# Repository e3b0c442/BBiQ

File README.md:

# BBiQ
Bespoke internet-connected barbecue thermometer

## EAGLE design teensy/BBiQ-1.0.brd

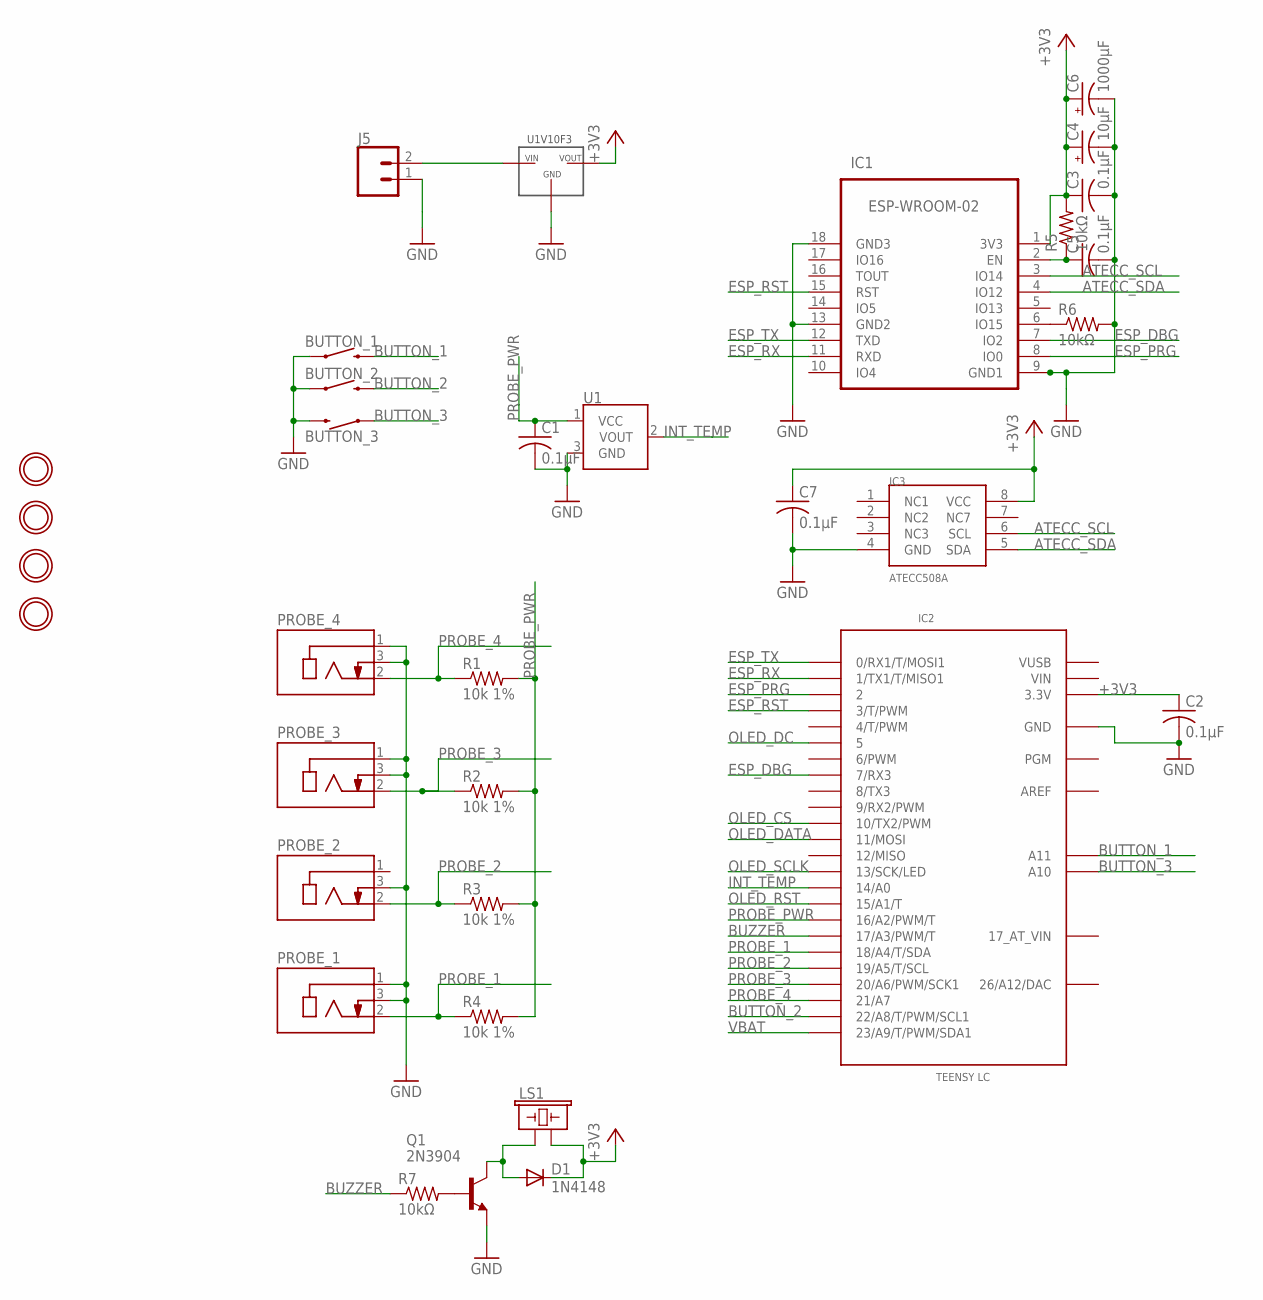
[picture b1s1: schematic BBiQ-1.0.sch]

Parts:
BUTTON_1, BUTTON_2, BUTTON_3: MOMENTARY-SWITCH-SPST-PTH-6.0MM; TACTILE_SWITCH_PTH_6.0MM
C1, C2, C3, C5, C7: 0.1µF; C025-025X050
C4: 10µF; E2-5
C6: 1000µF; E3,5-8
D1: 1N4148; DO35-7
IC1: ESP-WROOM-02
IC2: TEENSY LC; TEENSY_3.0-3.2&LC_ALL_PINS
IC3: ATECC508A; SOIC8
J5: CONN_02JST-PTH-2; JST-2-PTH
LS1: BUZZER-PTH; BUZZER-12MM
PROBE_1, PROBE_2, PROBE_3, PROBE_4: MJ-2506N; CUI_MJ-2506N
Q1: 2N3904; TO92
R1, R2, R3, R4: 10k 1%; 0207/7
R5, R6, R7: 10kΩ; 0207/7
U1: TMP36GT9; TO-92
U$2: U1V10F3
U$3, U$4, U$5, U$6: MOUNTINGHOLE2.5; MOUNTINGHOLE_2.5_PLATED

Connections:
26/A12/DAC: IC2.RESET/DAC (26/A12/DAC)
+3V3: C2.1, C3.1, C4.+, C6.+, C7.1, D1.C, IC1.1 (3V3), IC2.3.3V, IC2.3.3V1 (3.3V), IC3.8 (VCC), LS1.- (2), R5.2, U$2.VOUT
AREF: IC2.AREF
ATECC_SCL: IC1.3 (IO14), IC3.6 (SCL)
ATECC_SDA: IC1.4 (IO12), IC3.5 (SDA)
BUTTON_1: BUTTON_1.3 (2), IC2.A11
BUTTON_2: BUTTON_2.3 (2), IC2.22/A8 (22/A8/T/PWM/SCL1)
BUTTON_3: BUTTON_3.1, IC2.A10
BUZZER: IC2.17/A3 (17/A3/PWM/T), R7.1
ESP_DBG: IC1.7 (IO2), IC2.7 (7/RX3)
ESP_EN: C5.1, IC1.2 (EN), R5.1
ESP_PRG: IC1.8 (IO0), IC2.2
ESP_RST: IC1.15 (RST), IC2.3 (3/T/PWM)
ESP_RX: IC1.11 (RXD), IC2.1 (1/TX1/T/MISO1)
ESP_TX: IC1.12 (TXD), IC2.0 (0/RX1/T/MOSI1)
GND: BUTTON_1.1, BUTTON_2.1, BUTTON_3.3 (2), C1.2, C2.2, C3.2, C4.-, C5.2, C6.-, C7.2, IC1.9 (GND1), IC1.13 (GND2), IC1.18 (GND3), IC1.19 (GND0), IC2.AGND (GND), IC2.GND, IC2.GND1 (GND), IC3.4 (GND), J5.1, PROBE_1.1, PROBE_1.3, PROBE_2.3, PROBE_3.1, PROBE_3.3, PROBE_4.1, PROBE_4.3, Q1.3 (E), R6.2, U1.3 (GND), U$2.GND
INT_TEMP: IC2.14/A0, U1.2 (VOUT)
unnamed: IC1.6 (IO15), R6.1
unnamed: Q1.2 (B), R7.2
unnamed: D1.A, LS1.+ (1), Q1.1 (C)
OLED_CS: IC2.10 (10/TX2/PWM)
OLED_DATA: IC2.11 (11/MOSI)
OLED_DC: IC2.5
OLED_RST: IC2.15/A1 (15/A1/T)
OLED_SCLK: IC2.13 (13/SCK/LED)
PROBE_1: IC2.18/A4 (18/A4/T/SDA), PROBE_1.2, R4.1
PROBE_2: IC2.19/A5 (19/A5/T/SCL), PROBE_2.2, R3.1
PROBE_3: IC2.20/A6 (20/A6/PWM/SCK1), PROBE_3.2, R2.1
PROBE_4: IC2.21/A7, PROBE_4.2, R1.1
PROBE_PWR: C1.1, IC2.16/A2 (16/A2/PWM/T), R1.2, R2.2, R3.2, R4.2, U1.1 (VCC)
VBAT: IC2.23/A9 (23/A9/T/PWM/SDA1), J5.2, U$2.VIN
VIN: IC2.VIN
VUSB: IC2.VUSB

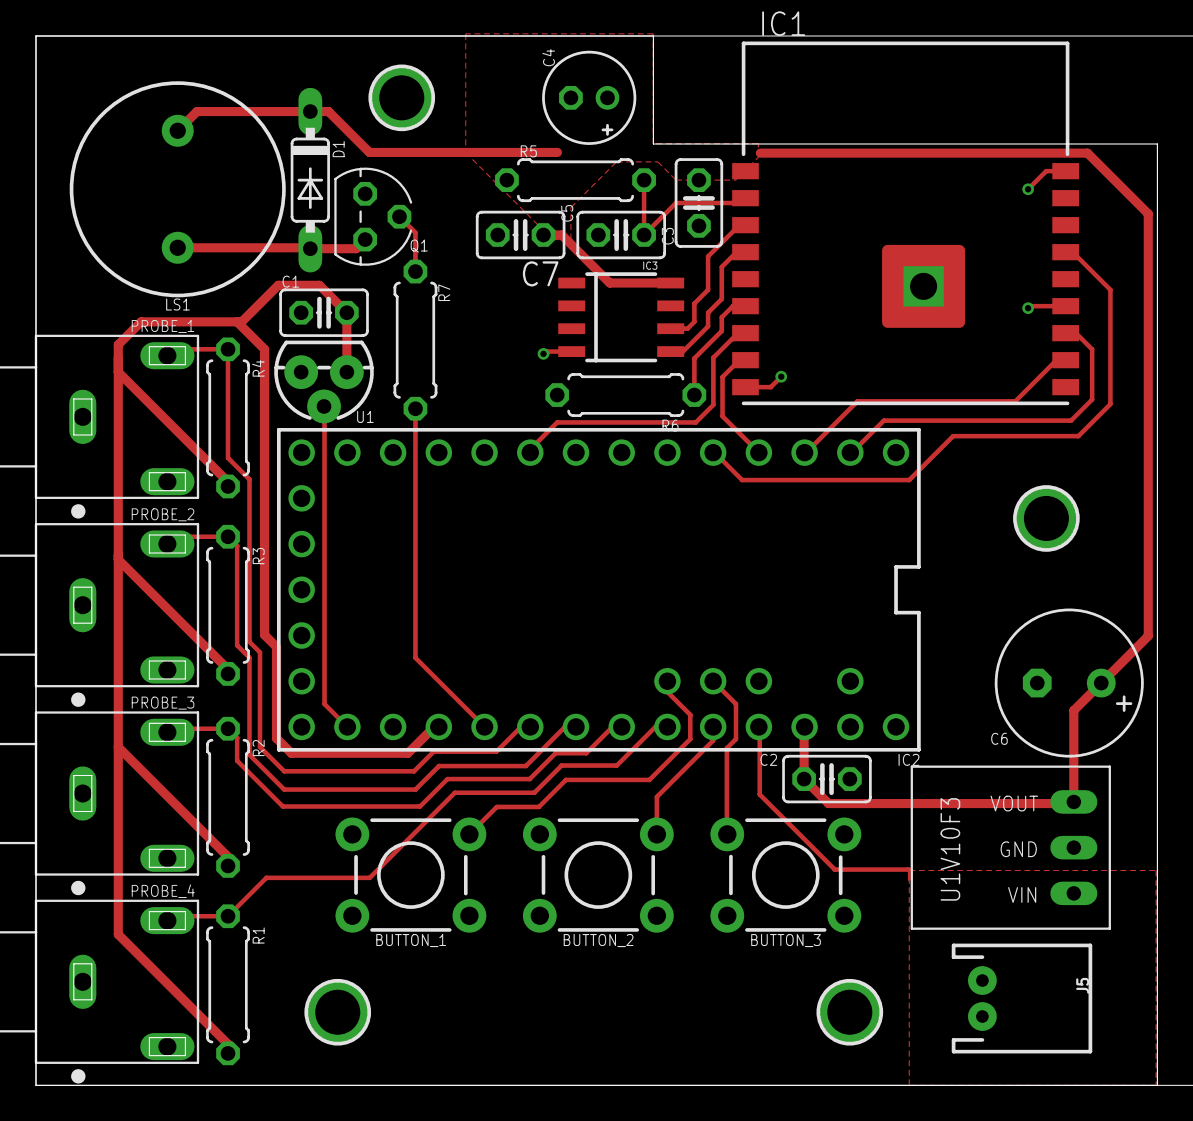
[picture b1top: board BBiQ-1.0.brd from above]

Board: 2 copper layers, 62.3 x 58.3 mm, 34 parts (0 on the bottom side), 24 nets.

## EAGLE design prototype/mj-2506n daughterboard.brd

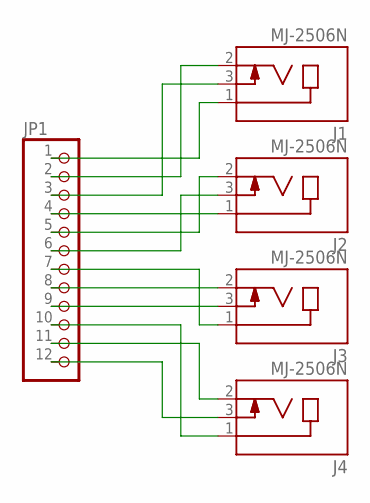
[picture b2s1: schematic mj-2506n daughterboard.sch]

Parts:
J1, J2, J3, J4: MJ-2506N; CUI_MJ-2506N
JP1: PINHD-1X12; 1X12

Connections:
unnamed: J1.1, JP1.1
unnamed: J1.3, JP1.3
unnamed: J1.2, JP1.2
unnamed: J2.1, JP1.4
unnamed: J2.3, JP1.6
unnamed: J2.2, JP1.5
unnamed: J3.2, JP1.8
unnamed: J3.3, JP1.9
unnamed: J3.1, JP1.7
unnamed: J4.1, JP1.10
unnamed: J4.2, JP1.11
unnamed: J4.3, JP1.12

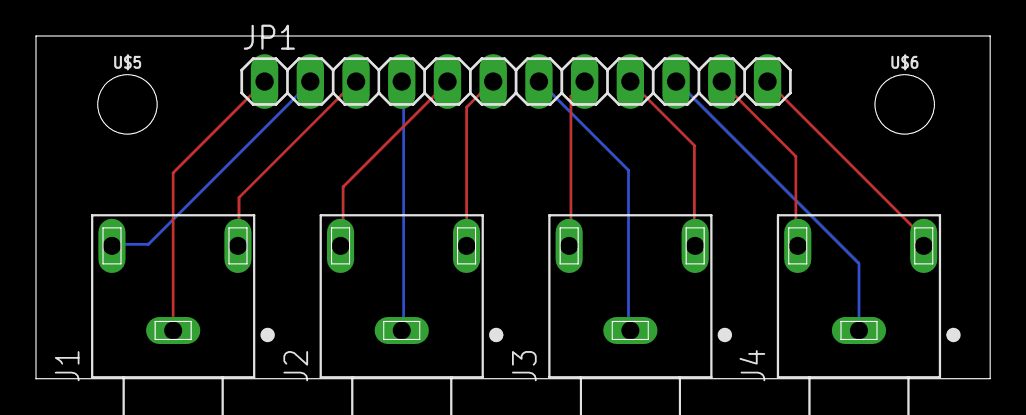
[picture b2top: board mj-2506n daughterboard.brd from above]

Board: 2 copper layers, 53.0 x 19.0 mm, 7 parts (0 on the bottom side), 12 nets.

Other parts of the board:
U$5, U$6: STAND-OFF

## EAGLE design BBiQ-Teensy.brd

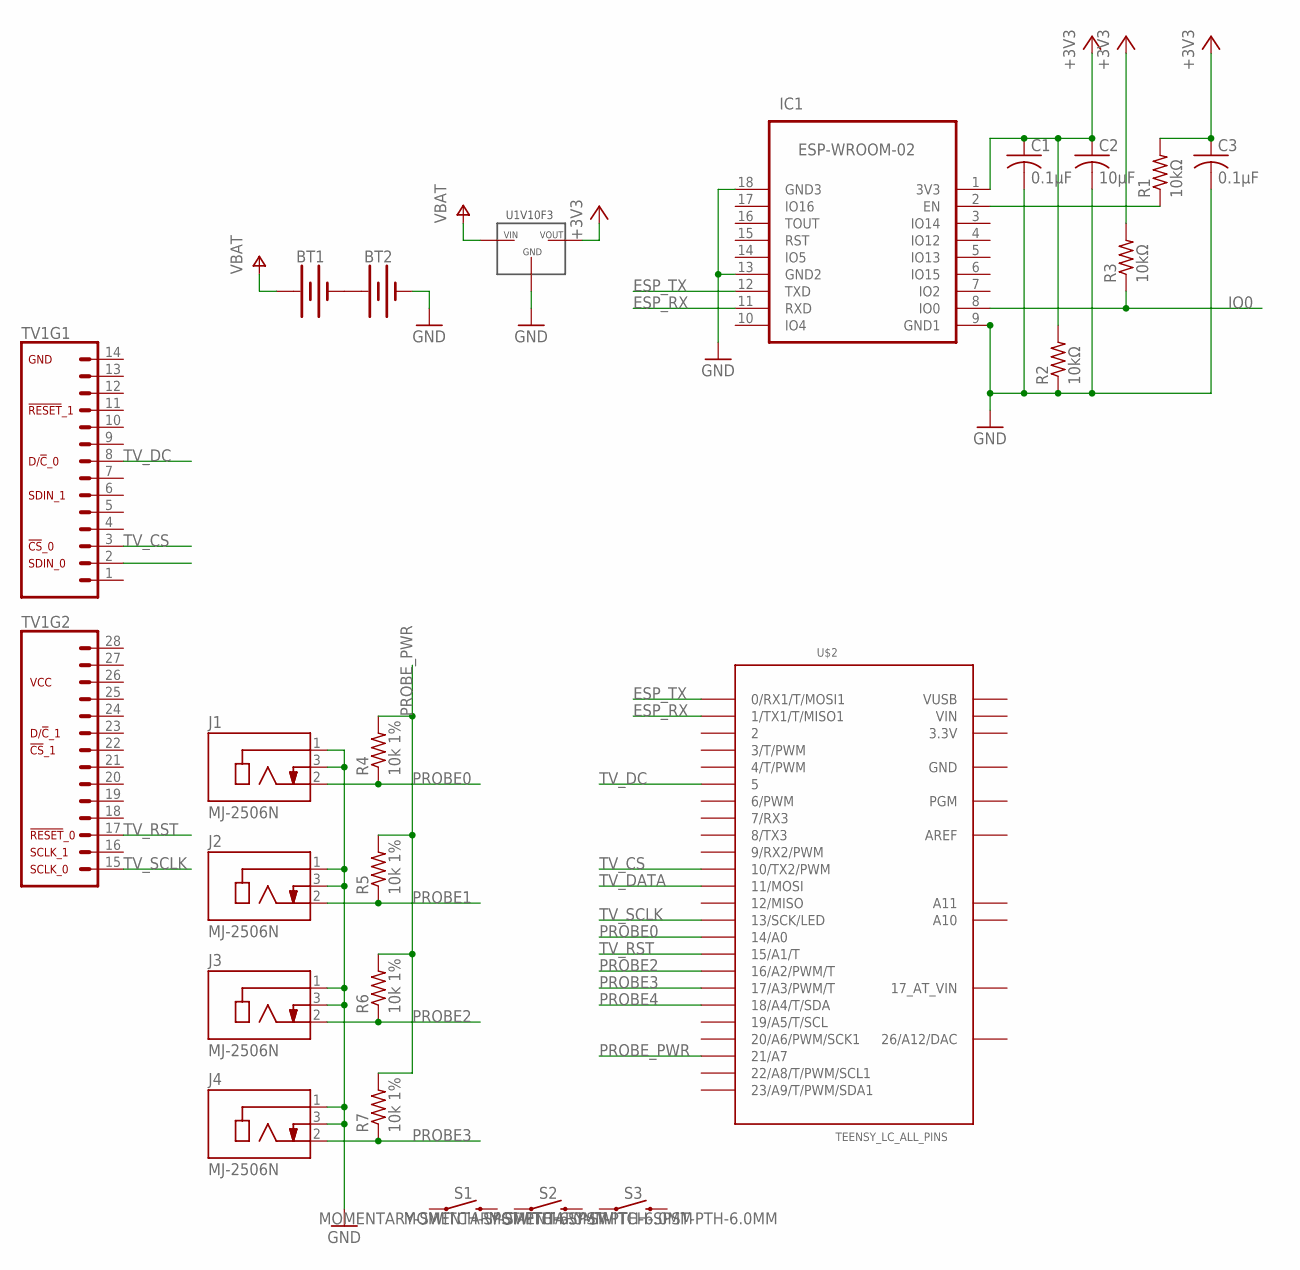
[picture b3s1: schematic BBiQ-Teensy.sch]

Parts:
BT1, BT2: BATTERY-AA
C1, C3: 0.1µF; C025-025X050
C2: 10µF; C025-025X050
IC1: ESP-WROOM-02
J1, J2, J3, J4: MJ-2506N; CUI_MJ-2506N
R1, R2, R3: 10kΩ; 0204/5
R4, R5, R6, R7: 10k 1%; 0204/5
S1, S2, S3: MOMENTARY-SWITCH-SPST-PTH-6.0MM; TACTILE_SWITCH_PTH_6.0MM
TV1: TEENSYVIEW
U$1: U1V10F3
U$2: TEENSY_LC_ALL_PINS; TEENSY_3.0-3.2&LC_ALL_PINS

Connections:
26/A12/DAC: U$2.RESET/DAC (26/A12/DAC)
+3V3: C1.1, C2.1, C3.1, IC1.1 (3V3), R1.2, R2.2, R3.2, U$1.VOUT, U$2.3.3V, U$2.3.3V1 (3.3V)
AREF: U$2.AREF
ESP_RX: IC1.11 (RXD), U$2.1 (1/TX1/T/MISO1)
ESP_TX: IC1.12 (TXD), U$2.0 (0/RX1/T/MOSI1)
GND: BT2.GND@1 (-), C1.2, C2.2, C3.2, IC1.9 (GND1), IC1.13 (GND2), IC1.18 (GND3), IC1.19 (GND0), J1.1, J1.3, J2.1, J2.3, J3.1, J3.3, J4.1, J4.3, R2.1, U$1.GND, U$2.AGND (GND), U$2.GND, U$2.GND1 (GND)
IO0: IC1.8 (IO0), R3.1
unnamed: BT1.GND@1 (-), BT2.PWR@1 (+)
unnamed: IC1.2 (EN), R1.1
PROBE0: J1.2, R4.1, U$2.14/A0
PROBE1: J2.2, R5.1
PROBE2: J3.2, R6.1, U$2.16/A2 (16/A2/PWM/T)
PROBE3: J4.2, R7.1, U$2.17/A3 (17/A3/PWM/T)
PROBE4: U$2.18/A4 (18/A4/T/SDA)
PROBE_PWR: R4.2, R5.2, R6.2, R7.2, U$2.21/A7
TV_CS: TV1.3, U$2.10 (10/TX2/PWM)
TV_DATA: TV1.2, U$2.11 (11/MOSI)
TV_DC: TV1.8, U$2.5
TV_RST: TV1.17 (3), U$2.15/A1 (15/A1/T)
TV_SCLK: TV1.15 (1), U$2.13 (13/SCK/LED)
V+: BT1.PWR@1 (+), U$1.VIN
VIN: U$2.VIN
VUSB: U$2.VUSB

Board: 2 copper layers, 23 parts (3 on the bottom side), 18 nets, no tracks yet.

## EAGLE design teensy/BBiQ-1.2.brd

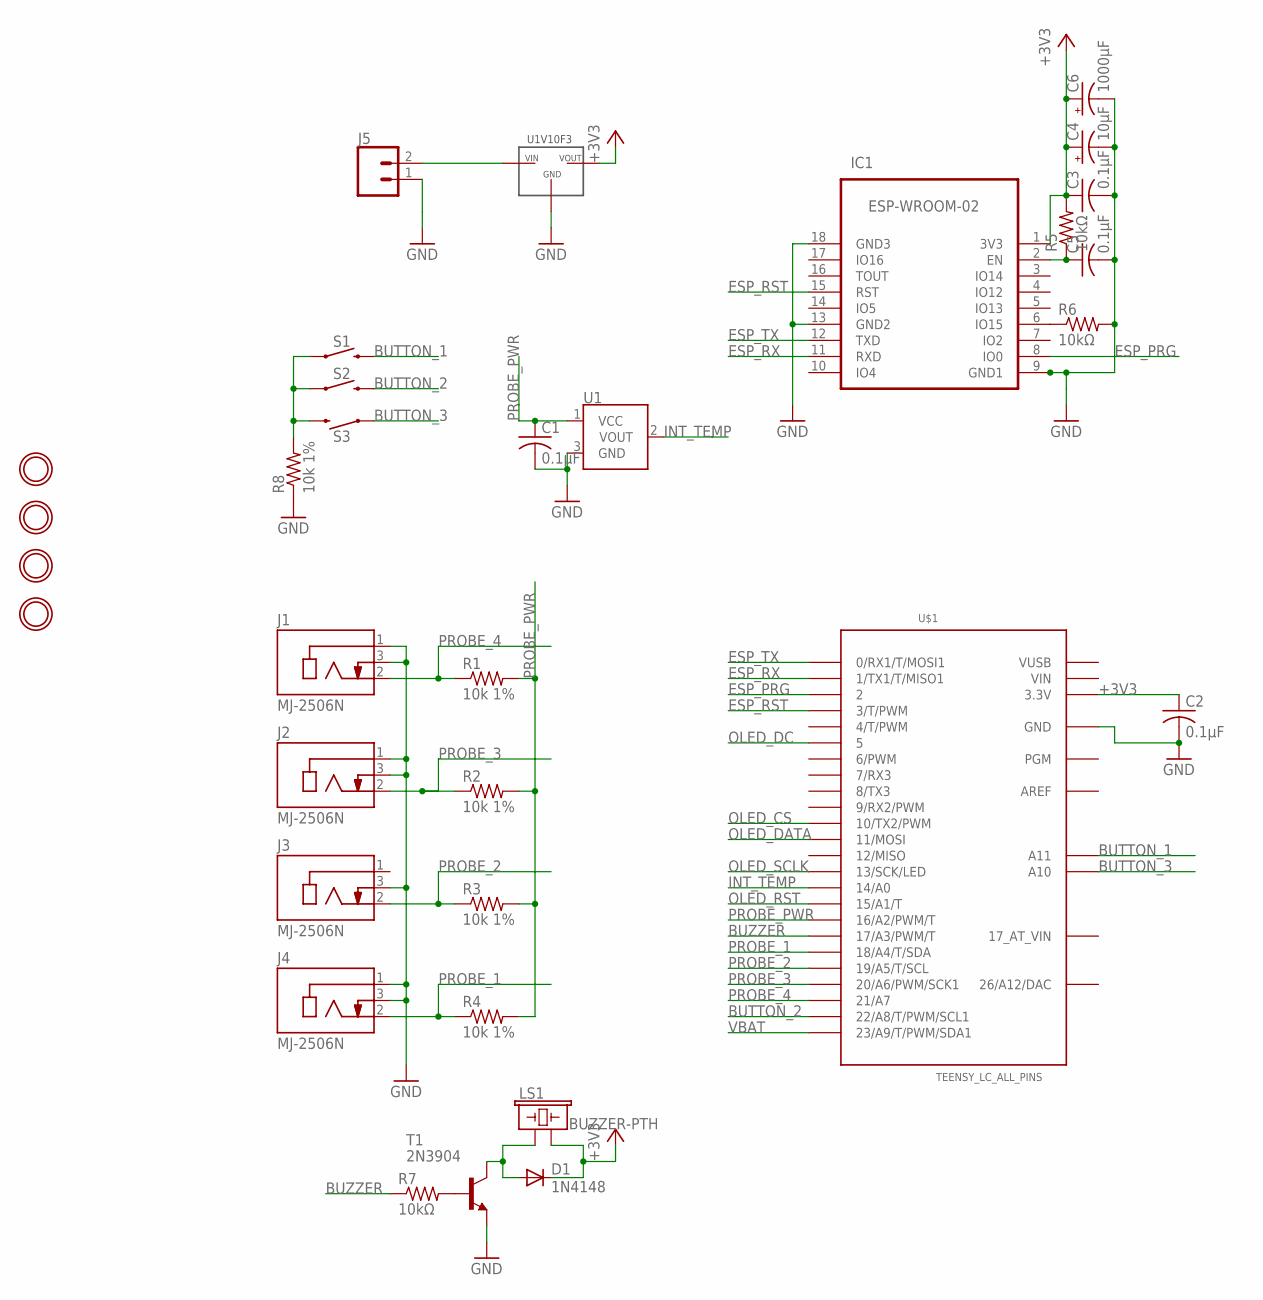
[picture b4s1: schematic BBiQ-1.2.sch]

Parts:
C1, C2, C3, C5: 0.1µF; C025-025X050
C4: 10µF; E2-5
C6: 1000µF; E3,5-8
D1: 1N4148; DO35-7
IC1: ESP-WROOM-02
J1, J2, J3, J4: MJ-2506N; CUI_MJ-2506N
J5: CONN_02JST-PTH-2; JST-2-PTH
LS1: BUZZER-PTH; BUZZER-12MM
R1, R2, R3, R4, R8: 10k 1%; 0207/7
R5, R6, R7: 10kΩ; 0207/7
S1, S2, S3: MOMENTARY-SWITCH-SPST-PTH-6.0MM; TACTILE_SWITCH_PTH_6.0MM
T1: 2N3904; TO92
U1: TMP36GT9; TO-92
U$1: TEENSY_LC_ALL_PINS; TEENSY_3.0-3.2&LC_ALL_PINS
U$2: U1V10F3
U$3, U$4, U$5, U$6: MOUNTINGHOLE2.5; MOUNTINGHOLE_2.5_PLATED

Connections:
26/A12/DAC: U$1.RESET/DAC (26/A12/DAC)
+3V3: C2.1, C3.1, C4.+, C6.+, D1.C, IC1.1 (3V3), LS1.- (2), R5.2, U$1.3.3V, U$1.3.3V1 (3.3V), U$2.VOUT
AREF: U$1.AREF
BUTTON_1: S1.3 (2), U$1.A11
BUTTON_2: S2.3 (2), U$1.22/A8 (22/A8/T/PWM/SCL1)
BUTTON_3: S3.1, U$1.A10
BUZZER: R7.1, U$1.17/A3 (17/A3/PWM/T)
ESP_EN: C5.1, IC1.2 (EN), R5.1
ESP_PRG: IC1.8 (IO0), U$1.2
ESP_RST: IC1.15 (RST), U$1.3 (3/T/PWM)
ESP_RX: IC1.11 (RXD), U$1.1 (1/TX1/T/MISO1)
ESP_TX: IC1.12 (TXD), U$1.0 (0/RX1/T/MOSI1)
GND: C1.2, C2.2, C3.2, C4.-, C5.2, C6.-, IC1.9 (GND1), IC1.13 (GND2), IC1.18 (GND3), IC1.19 (GND0), J1.1, J1.3, J2.1, J2.3, J3.3, J4.1, J4.3, J5.1, R6.2, R8.1, T1.3 (E), U1.3 (GND), U$1.AGND (GND), U$1.GND, U$1.GND1 (GND), U$2.GND
INT_TEMP: U1.2 (VOUT), U$1.14/A0
unnamed: IC1.6 (IO15), R6.1
unnamed: R7.2, T1.2 (B)
unnamed: D1.A, LS1.+ (1), T1.1 (C)
unnamed: R8.2, S1.1, S2.1, S3.3 (2)
OLED_CS: U$1.10 (10/TX2/PWM)
OLED_DATA: U$1.11 (11/MOSI)
OLED_DC: U$1.5
OLED_RST: U$1.15/A1 (15/A1/T)
OLED_SCLK: U$1.13 (13/SCK/LED)
PROBE_1: J4.2, R4.1, U$1.18/A4 (18/A4/T/SDA)
PROBE_2: J3.2, R3.1, U$1.19/A5 (19/A5/T/SCL)
PROBE_3: J2.2, R2.1, U$1.20/A6 (20/A6/PWM/SCK1)
PROBE_4: J1.2, R1.1, U$1.21/A7
PROBE_PWR: C1.1, R1.2, R2.2, R3.2, R4.2, U1.1 (VCC), U$1.16/A2 (16/A2/PWM/T)
VBAT: J5.2, U$1.23/A9 (23/A9/T/PWM/SDA1), U$2.VIN
VIN: U$1.VIN
VUSB: U$1.VUSB

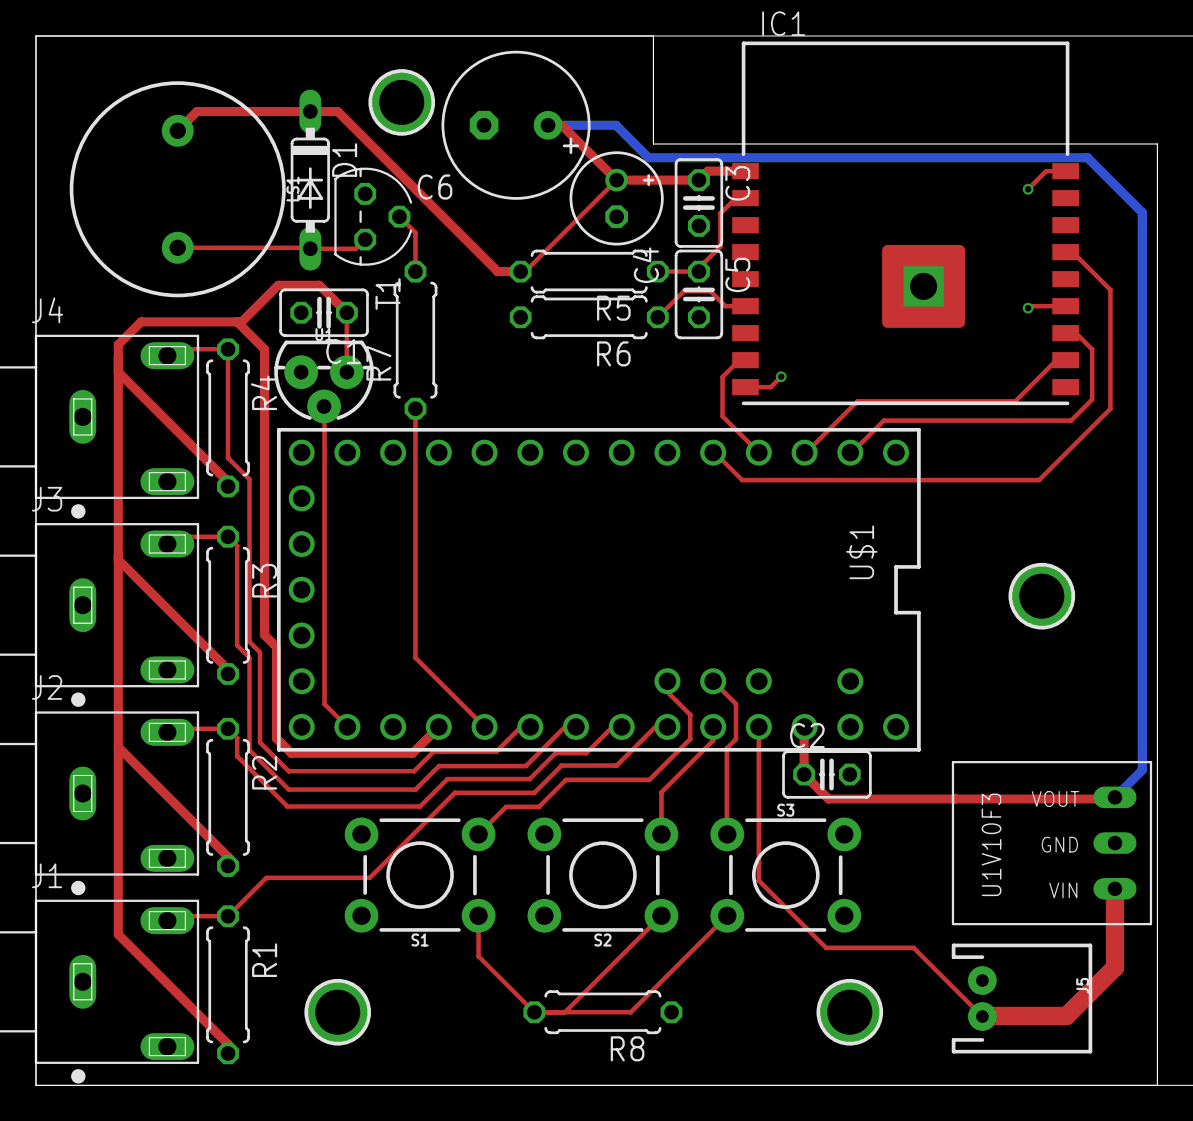
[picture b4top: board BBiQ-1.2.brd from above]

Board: 2 copper layers, 62.3 x 58.3 mm, 33 parts (0 on the bottom side), 22 nets.

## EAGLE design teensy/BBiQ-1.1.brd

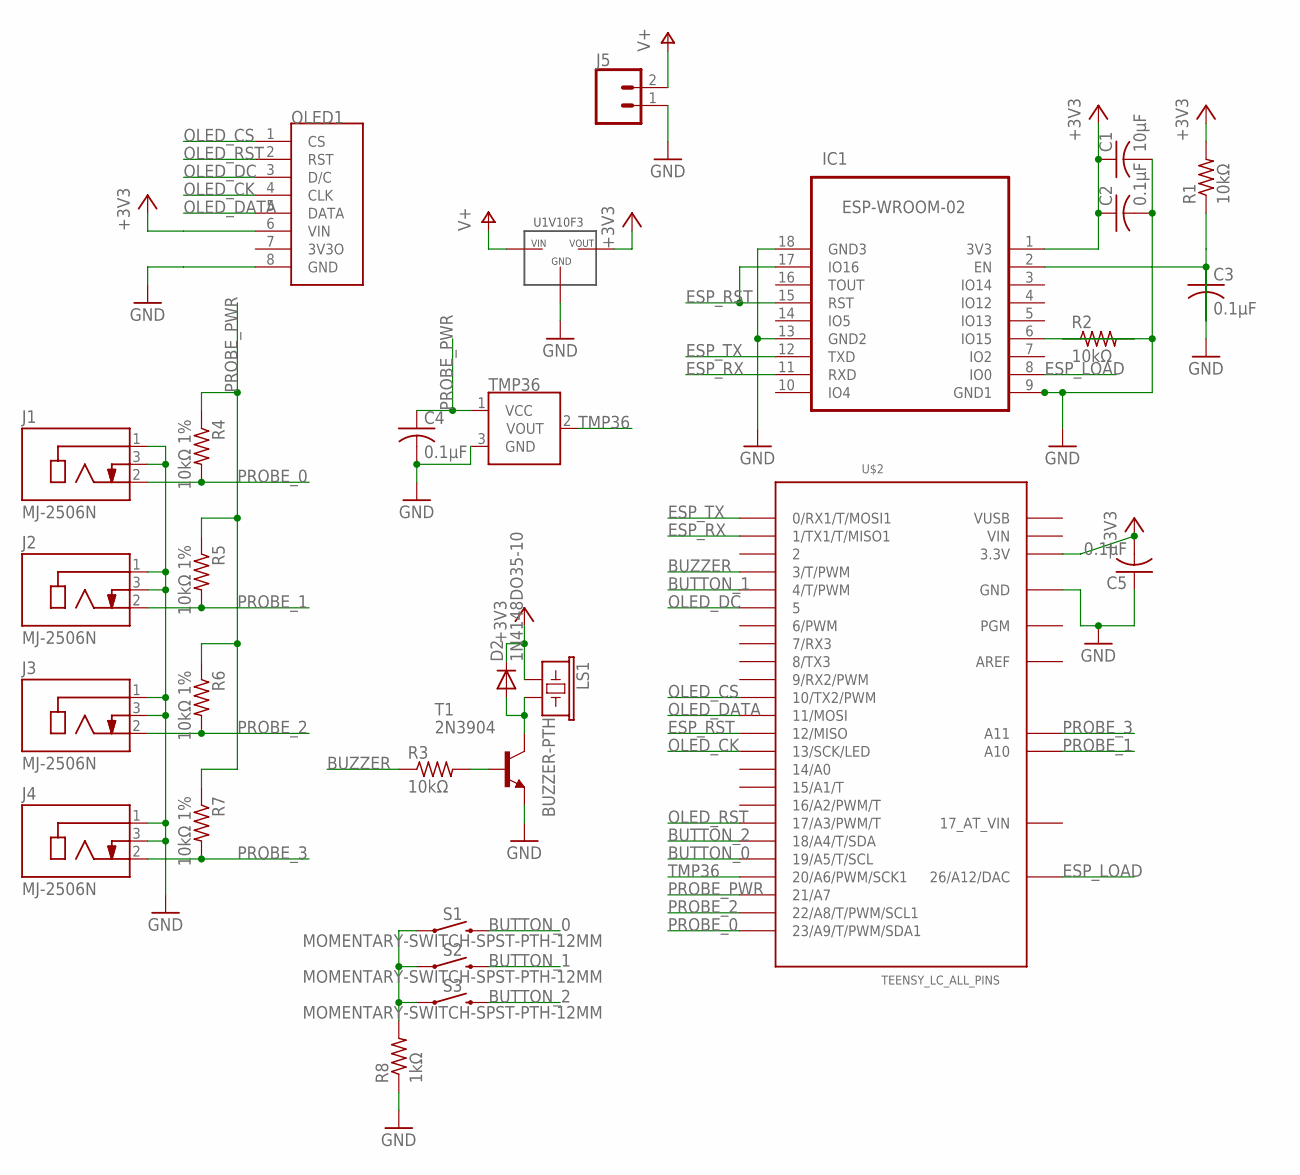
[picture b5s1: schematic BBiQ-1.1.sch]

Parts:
C1: 10µF; C025-025X050
C2, C3, C4, C5: 0.1µF; C025-025X050
D2: 1N4148DO35-10; DO35-10
IC1: ESP-WROOM-02
J1, J2, J3, J4: MJ-2506N; CUI_MJ-2506N
J5: CONN_02JST-PTH-2; JST-2-PTH
LS1: BUZZER-PTH; BUZZER-12MM
OLED1: ADAFRUIT_128X32_SPI_OLED
R1, R2, R3: 10kΩ; 0204/5
R4, R5, R6, R7: 10kΩ 1%; 0204/5
R8: 1kΩ; 0204/5
S1, S2, S3: MOMENTARY-SWITCH-SPST-PTH-12MM; TACTILE_SWITCH_PTH_12MM
T1: 2N3904; TO92
TMP36: TMP36GT9; TO-92
U$1: U1V10F3
U$2: TEENSY_LC_ALL_PINS; TEENSY_3.0-3.2&LC_ALL_PINS

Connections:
3V3O: OLED1.7 (3V3O)
+3V3: C1.1, C2.1, C5.2, D2.C, IC1.1 (3V3), LS1.+ (1), OLED1.6 (VIN), R1.2, U$1.VOUT, U$2.3.3V, U$2.3.3V1 (3.3V)
AREF: U$2.AREF
BUTTON_0: S1.3 (2), S1.4 (2), U$2.19/A5 (19/A5/T/SCL)
BUTTON_1: S2.3 (2), S2.4 (2), U$2.4 (4/T/PWM)
BUTTON_2: S3.3 (2), S3.4 (2), U$2.18/A4 (18/A4/T/SDA)
BUZZER: R3.1, U$2.3 (3/T/PWM)
ESP_LOAD: IC1.8 (IO0), U$2.RESET/DAC (26/A12/DAC)
ESP_RST: IC1.15 (RST), IC1.17 (IO16), U$2.12 (12/MISO)
ESP_RX: IC1.11 (RXD), U$2.1 (1/TX1/T/MISO1)
ESP_TX: IC1.12 (TXD), U$2.0 (0/RX1/T/MOSI1)
GND: C1.2, C2.2, C3.1, C4.2, C5.1, IC1.9 (GND1), IC1.13 (GND2), IC1.18 (GND3), IC1.19 (GND0), J1.1, J1.3, J2.1, J2.3, J3.1, J3.3, J4.1, J4.3, J5.1, OLED1.8 (GND), R2.1, R8.1, T1.3 (E), TMP36.3 (GND), U$1.GND, U$2.AGND (GND), U$2.GND, U$2.GND1 (GND)
unnamed: C3.2, IC1.2 (EN), R1.1
unnamed: IC1.6 (IO15), R2.2
unnamed: R3.2, T1.2 (B)
unnamed: D2.A, LS1.- (2), T1.1 (C)
unnamed: R8.2, S1.1, S1.2 (1), S2.1, S2.2 (1), S3.1, S3.2 (1)
OLED_CK: OLED1.4 (CLK), U$2.13 (13/SCK/LED)
OLED_CS: OLED1.1 (CS), U$2.10 (10/TX2/PWM)
OLED_DATA: OLED1.5 (DATA), U$2.11 (11/MOSI)
OLED_DC: OLED1.3 (D/C), U$2.5
OLED_RST: OLED1.2 (RST), U$2.17/A3 (17/A3/PWM/T)
PROBE_0: J1.2, R4.2, U$2.23/A9 (23/A9/T/PWM/SDA1)
PROBE_1: J2.2, R5.2, U$2.A10
PROBE_2: J3.2, R6.2, U$2.22/A8 (22/A8/T/PWM/SCL1)
PROBE_3: J4.2, R7.2, U$2.A11
PROBE_PWR: C4.1, R4.1, R5.1, R6.1, R7.1, TMP36.1 (VCC), U$2.21/A7
TMP36: TMP36.2 (VOUT), U$2.20/A6 (20/A6/PWM/SCK1)
VBAT: J5.2, U$1.VIN
VIN: U$2.VIN
VUSB: U$2.VUSB

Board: 2 copper layers, 29 parts (7 on the bottom side), 27 nets, no tracks yet.

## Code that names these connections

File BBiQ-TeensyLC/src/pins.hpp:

#pragma once

#include <Arduino.h>

enum class Pin : uint8_t
{
    ESP_TXD = 0,
    ESP_UART0_TXD = 0,
    ESP_GPIO1 = 0,

    ESP_RXD,
    ESP_UART0_RXD = 1,
    ESP_GPIO3 = 1,

    ESP_IO0,
    ESP_GPIO0 = 2,

    ESP_RST = 3,

    OLED_DC = 5,

    ESP_IO2 = 7,
    ESP_UART1_TXD = 7,

    OLED_CS = 10,

    OLED_MOSI = 11,

    OLED_SCK = 13,

    INT_TEMP = 14,

    OLED_RST = 15,

    PROBE_POWER = 16,

    BUZZER = 17,

    PROBE_1 = 18,

    PROBE_2 = 19,

    PROBE_3 = 20,

    PROBE_4 = 21,

    BUTTON_2 = 8, // breadboard; final = 22,

    BUTTON_1 = 9, // breadboard; final = 24,

    BUTTON_3 = 6, // breadboard; final = 25,
};

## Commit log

2018-07-06 prototype schematic
2018-07-06 forgot TMP36
2018-07-06 fixes
2018-07-07 view
2018-07-07 WIP, crashing
2018-07-07 cleanup
2018-07-07 all loops
2018-07-08 events are working now
2018-07-13 clean build, revamped UI
2018-07-14 PlatformIO
2018-07-14 Checkpoint - display and events working great!
2018-07-14 remove old source folder
2018-07-15 Local code complete! MILESTONE!
2018-07-18 firmata
2018-07-19 change
2018-07-20 schematic
2018-07-20 superfluous
2018-08-01 new board with teensyview
2018-08-01 remove images
2018-08-01 tweaks
2018-08-14 New projects for final TeensyLC/ESP-WROOM-02 code
2019-01-04 Teensy loader
2019-01-06 Add Teensy loader and Blynk apps
2019-01-09 Blow up and rebuild from scratch
2019-01-12 Update flasher; initial Blynk reimplementation to expose connection
2019-01-12 RPC wip
2019-01-13 2-way RPC
2019-01-14 redo loader
2019-01-14 Fix merge effup
2019-01-14 fix crash
2019-01-21 teensylicious
2019-01-21 Reset loader, move actual project
2019-01-24 Add initial button implementation, button combos to reset
2019-01-24 Display starter
2019-01-27 probes
2019-01-27 esp debug
2019-01-27 probe connect/disconnect reaction
2019-01-28 switch probes - button
2019-01-28 Mode handling for display and probes
2019-01-29 checkpoint before state redux
2019-02-05 New Teensy build
2019-02-06 RPC skeleton code
2019-02-06 board updates
2019-02-11 buzzer, pointers->references

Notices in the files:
parts and their libraries:
SparkFun-Batteries: Licensing: Creative Commons ShareAlike 4.0 International - https://creativecommons.org/licenses/by-sa/4.0
microbuilder: This work is placed in the public domain, and may be freely used for commercial and non-commercial work with the following conditions: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
